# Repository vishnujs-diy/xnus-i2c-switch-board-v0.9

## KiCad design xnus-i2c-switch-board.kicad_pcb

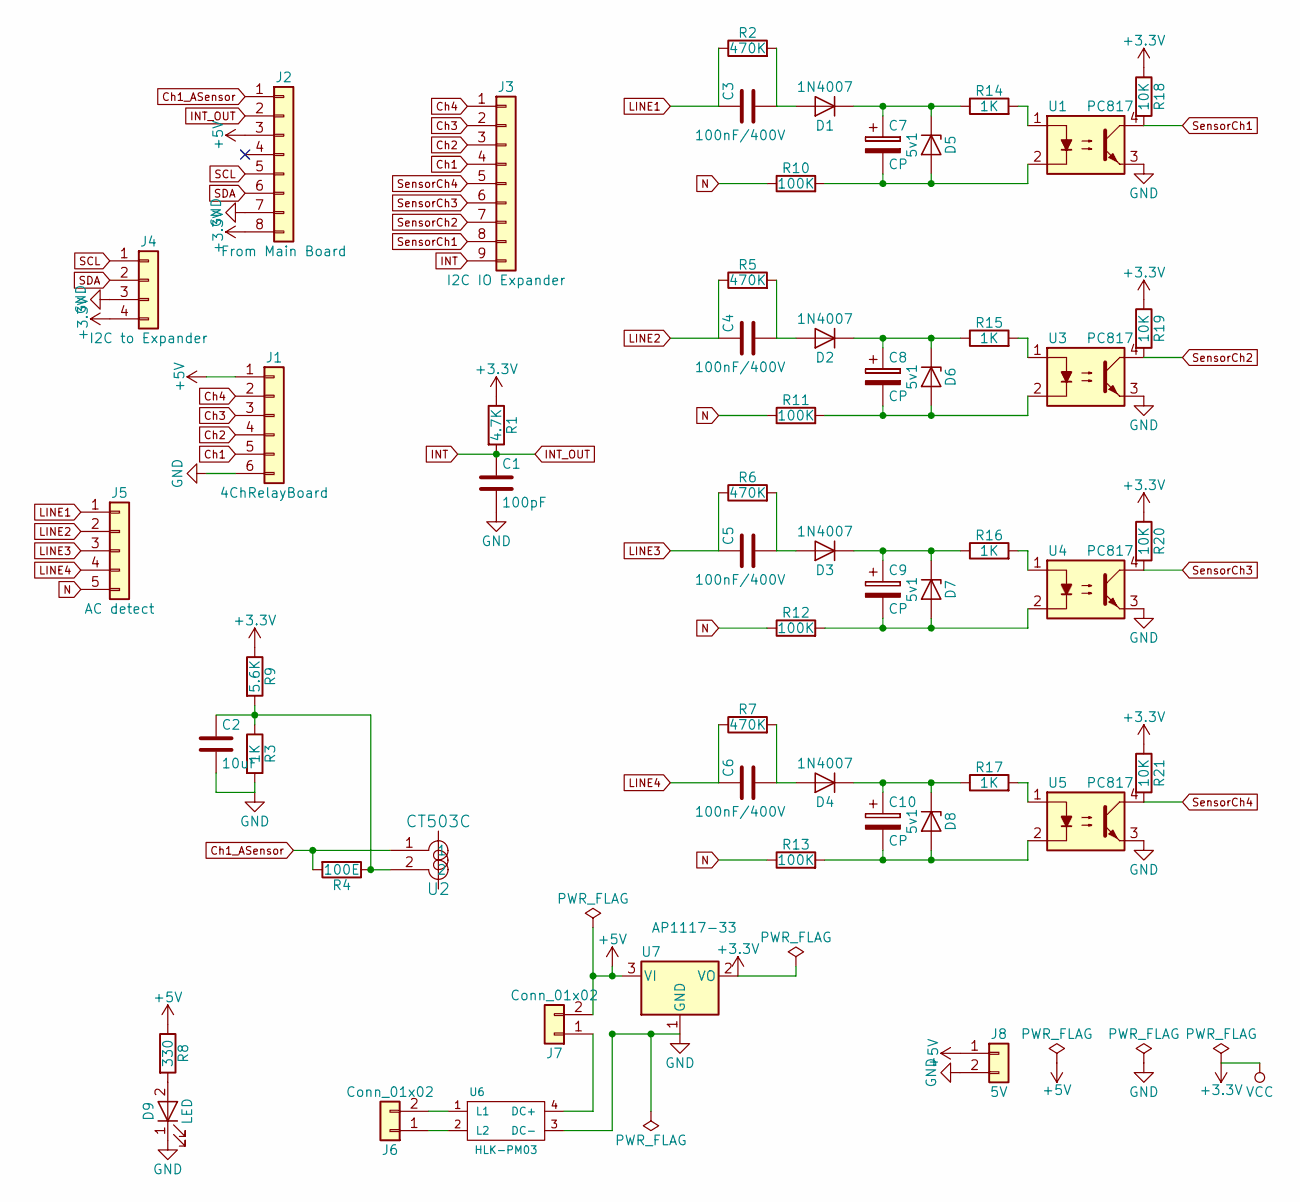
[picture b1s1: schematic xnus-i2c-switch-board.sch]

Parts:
C1: 100pF; C_Disc_D5.1mm_W3.2mm_P5.00mm
C2: 10uF; CP_Radial_D6.3mm_P2.50mm
C3, C4, C5, C6: 100nF/400V; C_Rect_L11.5mm_W6.4mm_P10.00mm_MKT
C7, C8, C9, C10: CP; CP_Radial_D5.0mm_P2.50mm
D1, D2, D3, D4: 1N4007; D_A-405_P2.54mm_Vertical_AnodeUp
D5, D6, D7, D8: 5v1; D_A-405_P2.54mm_Vertical_AnodeUp
D9: LED; LED_D1.8mm_W3.3mm_H2.4mm
J1: 4ChRelayBoard; Pin_Header_Straight_1x06_Pitch2.54mm
J2: From Main Board; Pin_Header_Straight_1x08_Pitch2.54mm
J3: I2C IO Expander; Pin_Header_Straight_1x09_Pitch2.54mm
J4: I2C to Expander; Pin_Header_Straight_1x04_Pitch2.54mm
J5: AC detect; TerminalBlock_bornier-5_P5.08mm
J6: Conn_01x02; TerminalBlock_bornier-2_P5.08mm
J7: Conn_01x02; Pin_Header_Straight_1x02_Pitch2.54mm
J8: 5V; JST_EH_B02B-EH-A_02x2.50mm_Straight
R1: 4.7K; R_Axial_DIN0207_L6.3mm_D2.5mm_P10.16mm_Horizontal
R2, R5, R6, R7: 470K; R_Axial_DIN0207_L6.3mm_D2.5mm_P2.54mm_Vertical
R3: 1K; R_Axial_DIN0207_L6.3mm_D2.5mm_P10.16mm_Horizontal
R4: 100E; R_Axial_DIN0207_L6.3mm_D2.5mm_P7.62mm_Horizontal
R8: 330; R_Axial_DIN0207_L6.3mm_D2.5mm_P5.08mm_Vertical
R9: 5.6K; R_Axial_DIN0207_L6.3mm_D2.5mm_P10.16mm_Horizontal
R10, R11, R12, R13: 100K; R_Axial_DIN0207_L6.3mm_D2.5mm_P2.54mm_Vertical
R14, R15, R16, R17: 1K; R_Axial_DIN0207_L6.3mm_D2.5mm_P2.54mm_Vertical
R18, R19, R20, R21: 10K; R_Axial_DIN0207_L6.3mm_D2.5mm_P2.54mm_Vertical
U1, U3, U4, U5: PC817; DIP-4_W7.62mm
U2: CT503C
U6: HLK-PM03; HLK-PM01
U7: AP1117-33; SOT-223-3_TabPin2

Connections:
+3V3: J2.8, J4.4, R1.1, R9.1, R18.1, R19.1, R20.1, R21.1, U7.2 (VO)
+5V: J1.1, J2.3, J7.2, J8.1, R8.1, U7.3 (VI)
Ch1: J1.5, J3.4
Ch1_ASensor: J2.1, R4.2, U2.1
Ch2: J1.4, J3.3
Ch3: J1.3, J3.2
Ch4: J1.2, J3.1
GND: C1.2, C2.2, D9.1 (K), J1.6, J2.7, J4.3, J8.2, R3.2, U1.3, U3.3, U4.3, U5.3, U6.3 (DC-), U7.1 (GND)
INT: C1.1, J2.2, J3.9, R1.2
LINE1: C3.1, J5.1, R2.1
LINE2: C4.1, J5.2, R5.1
LINE3: C5.1, J5.3, R6.1
LINE4: C6.1, J5.4, R7.1
N: J5.5, R10.1, R11.1, R12.1, R13.1
unnamed: C2.1, R3.1, R4.1, R9.2, U2.2
unnamed: C3.2, D1.2 (A), R2.2
unnamed: C4.2, D2.2 (A), R5.2
unnamed: C5.2, D3.2 (A), R6.2
unnamed: C6.2, D4.2 (A), R7.2
unnamed: C7.1, D1.1 (K), D5.1 (K), R14.1
unnamed: C7.2, D5.2 (A), R10.2, U1.2
unnamed: C8.1, D2.1 (K), D6.1 (K), R15.1
unnamed: C8.2, D6.2 (A), R11.2, U3.2
unnamed: C9.1, D3.1 (K), D7.1 (K), R16.1
unnamed: C9.2, D7.2 (A), R12.2, U4.2
unnamed: C10.1, D4.1 (K), D8.1 (K), R17.1
unnamed: C10.2, D8.2 (A), R13.2, U5.2
unnamed: D9.2 (A), R8.2
unnamed: J6.1, U6.2 (L2)
unnamed: J6.2, U6.1 (L1)
unnamed: J7.1, U6.4 (DC+)
unnamed: R14.2, U1.1
unnamed: R15.2, U3.1
unnamed: R16.2, U4.1
unnamed: R17.2, U5.1
SCL: J2.5, J4.1
SDA: J2.6, J4.2
SensorCh1: J3.8, R18.2, U1.4
SensorCh2: J3.7, R19.2, U3.4
SensorCh3: J3.6, R20.2, U4.4
SensorCh4: J3.5, R21.2, U5.4

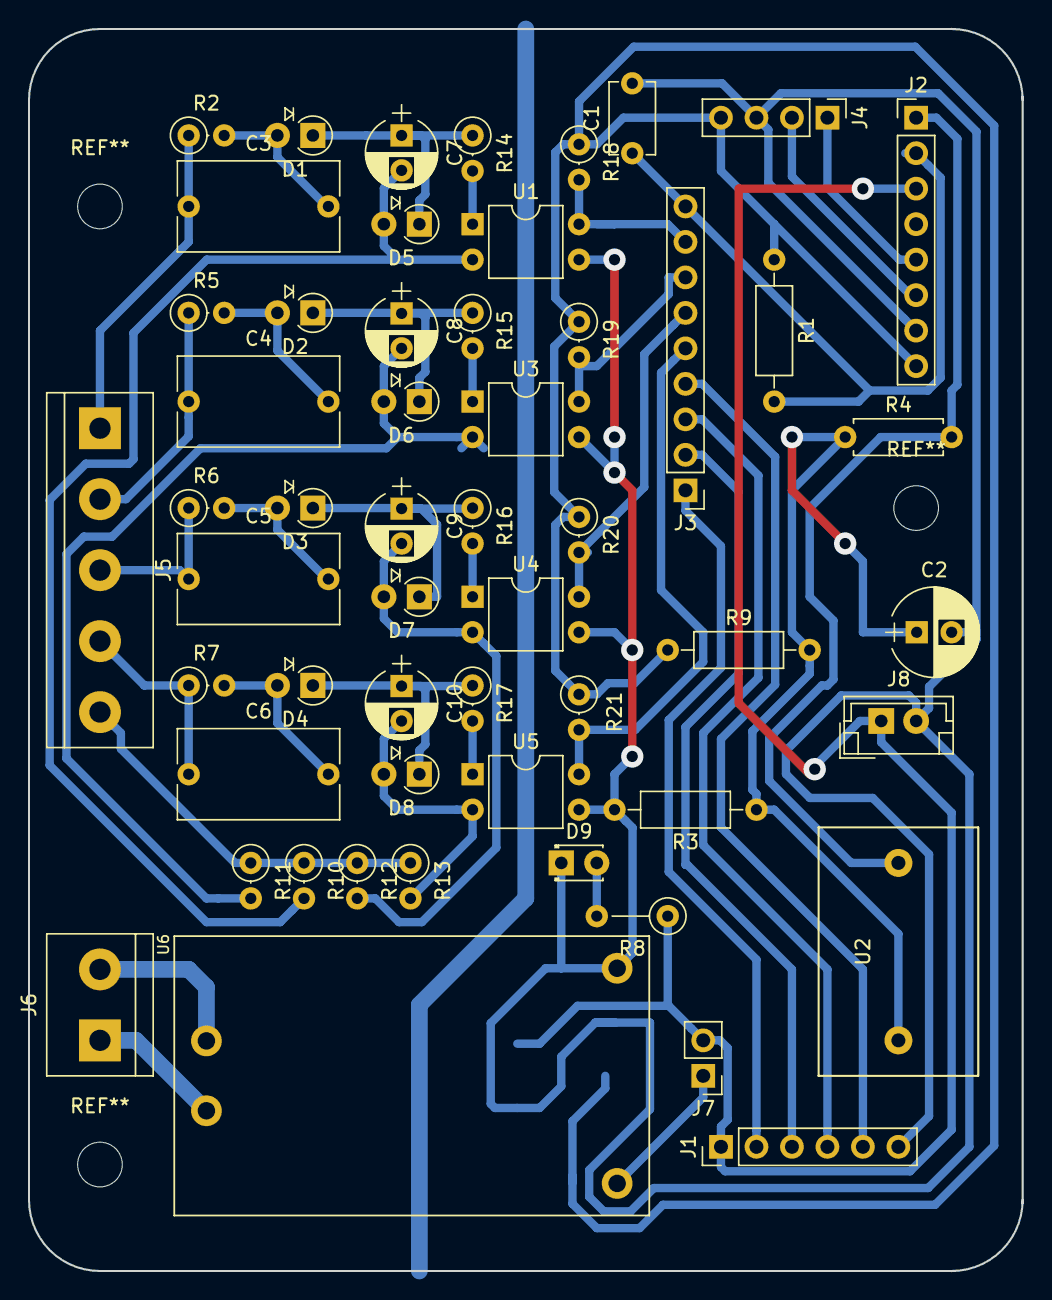
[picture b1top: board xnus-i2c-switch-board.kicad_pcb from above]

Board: 2 copper layers, 71.1 x 88.9 mm, 55 parts (1 on the bottom side), 41 nets.

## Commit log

2018-04-06 Adding 3D pic
